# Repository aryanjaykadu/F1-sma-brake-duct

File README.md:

# Passive SMA Brake Duct: feasibility study

Can a brake-cooling duct open and close itself, with no electronics, using a
shape-memory-alloy (Nitinol) spring heated by the brake disc?

The idea: louvers in the duct stay shut on the straights to cut drag, and a
spring heated by the rotor opens them after heavy braking.
I modelled the mechanism in SOLIDWORKS, ran thermal and aero CFD in ANSYS
Fluent, checked the structure in ANSYS MAPDL, and tested the actuator
behaviour over a simulated lap.

**Start here:** [Project Guidebook (PDF)](report/Project_Guidebook.pdf), which covers the problem, how it works, every
phase, tools, results and limits. A web version is in [docs/GUIDEBOOK.md](docs/GUIDEBOOK.md).

Product package: [one-page product sheet](report/SMA_Duct_Module_Product_Sheet.pdf),
[assembly drawing SMA-DM-001](cad/product/SMA-DM-001.pdf),
[design notes](docs/PRODUCT.md).

## What I found

| Question | Answer | Evidence |
|---|---|---|
| Does the linkage give enough stroke? | Yes: 14.0 mm rod travel for 80° of louver rotation | SOLIDWORKS mates, `cad/` |
| Is air near the rotor hot enough to trigger the spring? | No: 300-324 K against the 358 K needed | Fluent, `cfd/Temp_Contour_CaseA*.png` |
| Can rotor radiation trigger it? | Yes, if the wire is dark (emissivity ≥ ~0.45) | 119-129 kW/m² incident, `cfd/SMA_Wire_Temperature_CaseA.png` |
| Does it close again on the straight? | Yes: wire settles at 306-311 K | Fluent Case B |
| Does the specified 1.2 mm NiTi spring work over a lap? | No. It is too slow to heat and its hysteresis is too wide | `cfd/transient/` |
| Redesign | Six 0.5 mm NiTiCu springs (Af 76 °C, Mf 58 °C). They open after the 3 hardest braking zones and are open 2 % of straight-line time | `cfd/transient/`, `fea/pack_NiTiCu/` |
| Stresses OK? | Yes, lowest factor of safety 3.3 | MAPDL, `fea/` |
| Does closing the louvers cut drag by 18.4 %, as the brief assumed? | **No. With a rotating wheel on a moving road, closing them adds 0.5 % drag** | Isolated-wheel Fluent, `cfd/wheel/` |
| Where does the idea pay off? | On an EV grille shutter: closing it cuts drag 14.5 % on a simple CFD car, and about 3-5 % of battery energy on a real one | `ev/`, `docs/EV_COOLING.md` |

The drag result is the main finding, reached in three steps:

1. **Scale.** The duct's own through-flow drag is the momentum of the air it
   swallows: 0.155-0.183 kg/s × 83 m/s ≈ 13-15 N, or 1.1-1.4 % of total drag
   on every mesh. Closing the inlet also changes the outside flow
   (interference), so this is not a hard cap, but 18 % would need
   interference more than ten times larger.
2. **Mesh study, stationary wheel.** On 284k, 408k and 768k cells the
   open-vs-closed difference (-9.6 %, +5.2 %, -1.3 %) stayed within the
   solver noise from the unsteady wheel wake.
3. **Rotating wheel on a moving road, time-averaged over 160 ms of transient
   flow.** Closing the louvers *adds* 0.53 % drag (95 % interval +0.43 to
   +0.63 %). The duct's own drag falls by 0.4 N, but the wheel's rises by
   more.

The full numbers, method and limits are in [docs/RESULTS.md](docs/RESULTS.md),
and the write-up is in [report/ThermoKinetic_BrakeDuct_Whitepaper.pdf](report/ThermoKinetic_BrakeDuct_Whitepaper.pdf).

## Bench rig (designed and virtually tested, not built yet)

The next step is a bench rig that heats the spring pack the way the braking
rotor does and cools it the way the airflow does, so the simulations can be
checked against measurements. It has a halogen lamp standing in for the rotor
and a blower standing in for car speed, with thermocouples, a magnetic angle
sensor and a load cell. It consists of:

- **Rig CAD:** SOLIDWORKS assembly with zero interferences.
- **Electronics:** an Arduino Uno shield in KiCad. ERC and DRC are clean, and
  Gerbers are ready to order.
- **Firmware:** compiled for the Uno, using 57 % of flash and 55 % of RAM.
- **Digital twin:** runs the same firmware code against a physics model of the
  rig. The Phase 4 logger connects to it over a TCP "serial port".

| Virtual test | Twin result |
|---|---|
| Slow ramp hysteresis | Opens 72-75 °C, closes 63-60 °C, 11.5 °C wide (design 12 °C) |
| 0.5 mm vs 1.2 mm wire | Closes in 1.9 s vs 5.7 s |
| Car lap replayed on the rig | Same 3 openings per lap as the car model, 87 % open/closed agreement |
| 1,000 heat/cool cycles | All complete, no firmware faults (no fatigue model) |
| Sensor and cooling failures | Heater latches off in both cases |

The twin also caught design problems before anything was built:

- **Heater switching window:** at 1 s it distorted the hysteresis measurement,
  so it is now 200 ms.
- **Rig capacity:** the first layout was too weak to reproduce the car lap, so
  a blower was added and the lamp moved closer.
- **Phase 1 CAD bug:** the linkage rod was sitting on the wrong side of the duct.

Details are in [docs/RIG.md](docs/RIG.md).

## Product package

The actuator is also detailed as a product:
- **Module CAD:** production-level detail, including real helical NiTiCu
  springs with a black coating, a steel bias spring, anodised brackets and an
  inlet flange with M3 fasteners. 21 components, zero interferences.
- **Animation:** the springs genuinely stretch and contract as the louvers
  open and close.
- **Drawing:** A3 assembly drawing SMA-DM-001 with a parts list.
- **Product sheet:** one-page summary.
- **Rig CAD:** the bench rig now carries the real 3D circuit board exported
  from KiCad.

See [docs/PRODUCT.md](docs/PRODUCT.md).

## Re-target: passive grille shutter for an EV

F1 bans moving aero parts and the brake duct moves too little air to
matter, so I moved the same idea to where it can pay: an EV radiator
shutter. A low-temperature NiTi spring pack (As 35 / Af 40 °C) sits in the
coolant return line and opens six louvers when the coolant warms. It needs
no motor, sensor or wiring.

- **CFD, half car with a porous radiator and moving road:**
  - Closing the shutters cuts drag by 105 N at 100 km/h and 182 N at
    130 km/h, both 14.5 %. Iteration noise is under ±10 N, and the saving
    scales with V².
  - About three quarters of the saving is interference from the plain
    floor exit, not the radiator's own momentum drag.
- **Drive-cycle model, with cooling drag in the road load:**
  - At a production-car level of cooling drag the shutter saves 3.4 % of
    battery energy in the city and 5.4 % at 130 km/h. A motorised
    thermostat shutter saves 4.5 %.
  - On a 38 °C day it opens fully and the coolant peak matches an open
    grille.
- **Module CAD:** frame, six louvers, a scotch-yoke bar (14.8 mm lift for
  80°), the SMA pack in a clear coolant sleeve and a bias spring. Zero
  interferences shut and open.

See [docs/EV_COOLING.md](docs/EV_COOLING.md).

## Limits (read before quoting numbers)

- ANSYS Student licence: meshes are capped at 1M cells, so the CFD is coarse.
- Drag study: the rotating-wheel result is averaged over only 160 ms (about
  four wake cycles) on one mesh, and its 95 % interval covers sampling noise
  only. The drag coefficient (1.19) is still above real-wheel values.
- The lap model is reduced-order, on a synthetic lap trace, calibrated to two
  steady Fluent cases.
- The NiTiCu transformation temperatures are design targets, not a datasheet
  alloy.
- **No hardware was built or tested.** The bench file in `bench/` is a
  simulated dry run of the data logger, and the rig results in
  `bench/virtual/` come from the digital twin, not measurements.
- Moving aero parts are banned under the F1 technical regulations, so this
  is a research and non-FIA concept.

## Tools

SOLIDWORKS 2025, ANSYS Student 2026 R1 (Fluent, MAPDL), KiCad 10,
Arduino (Uno), C++, gmsh and Python.

## Repo layout

| Path | Contents |
|---|---|
| `phase1_*.py`, `swlib.py` | SOLIDWORKS parts and assembly |
| `phase2_*.py` | Fluent CHT domain, meshing, solves, radiation, lap model, wheel aero |
| `phase3_fea.py` | MAPDL linkage and stress model |
| `phase4_bench_validation.py` | DAQ logger (only run in simulation) |
| `phase5_generate_whitepaper.py` | Builds the PDF from the result files |
| `rig_cad.py`, `rig_import_pcb.py` | SOLIDWORKS bench rig parts and assembly, shield PCB import |
| `product_*.py` | Product module CAD, animation, drawing and product sheet |
| `electronics/` | KiCad shield: schematic and PCB generators, Gerbers, BOM |
| `firmware/` | Arduino firmware, lap-profile generator, digital twin and test campaign |
| `ev/` | EV grille-shutter re-target: sizing, half-car CFD, drive-cycle model, shutter CAD |
| `cad/`, `cfd/`, `fea/`, `bench/`, `report/` | Models, plots and result JSON |

Solver case and data files (several GB) are not included. Re-running needs
SOLIDWORKS and ANSYS installed. Run order is in
[docs/RESULTS.md](docs/RESULTS.md#re-running).

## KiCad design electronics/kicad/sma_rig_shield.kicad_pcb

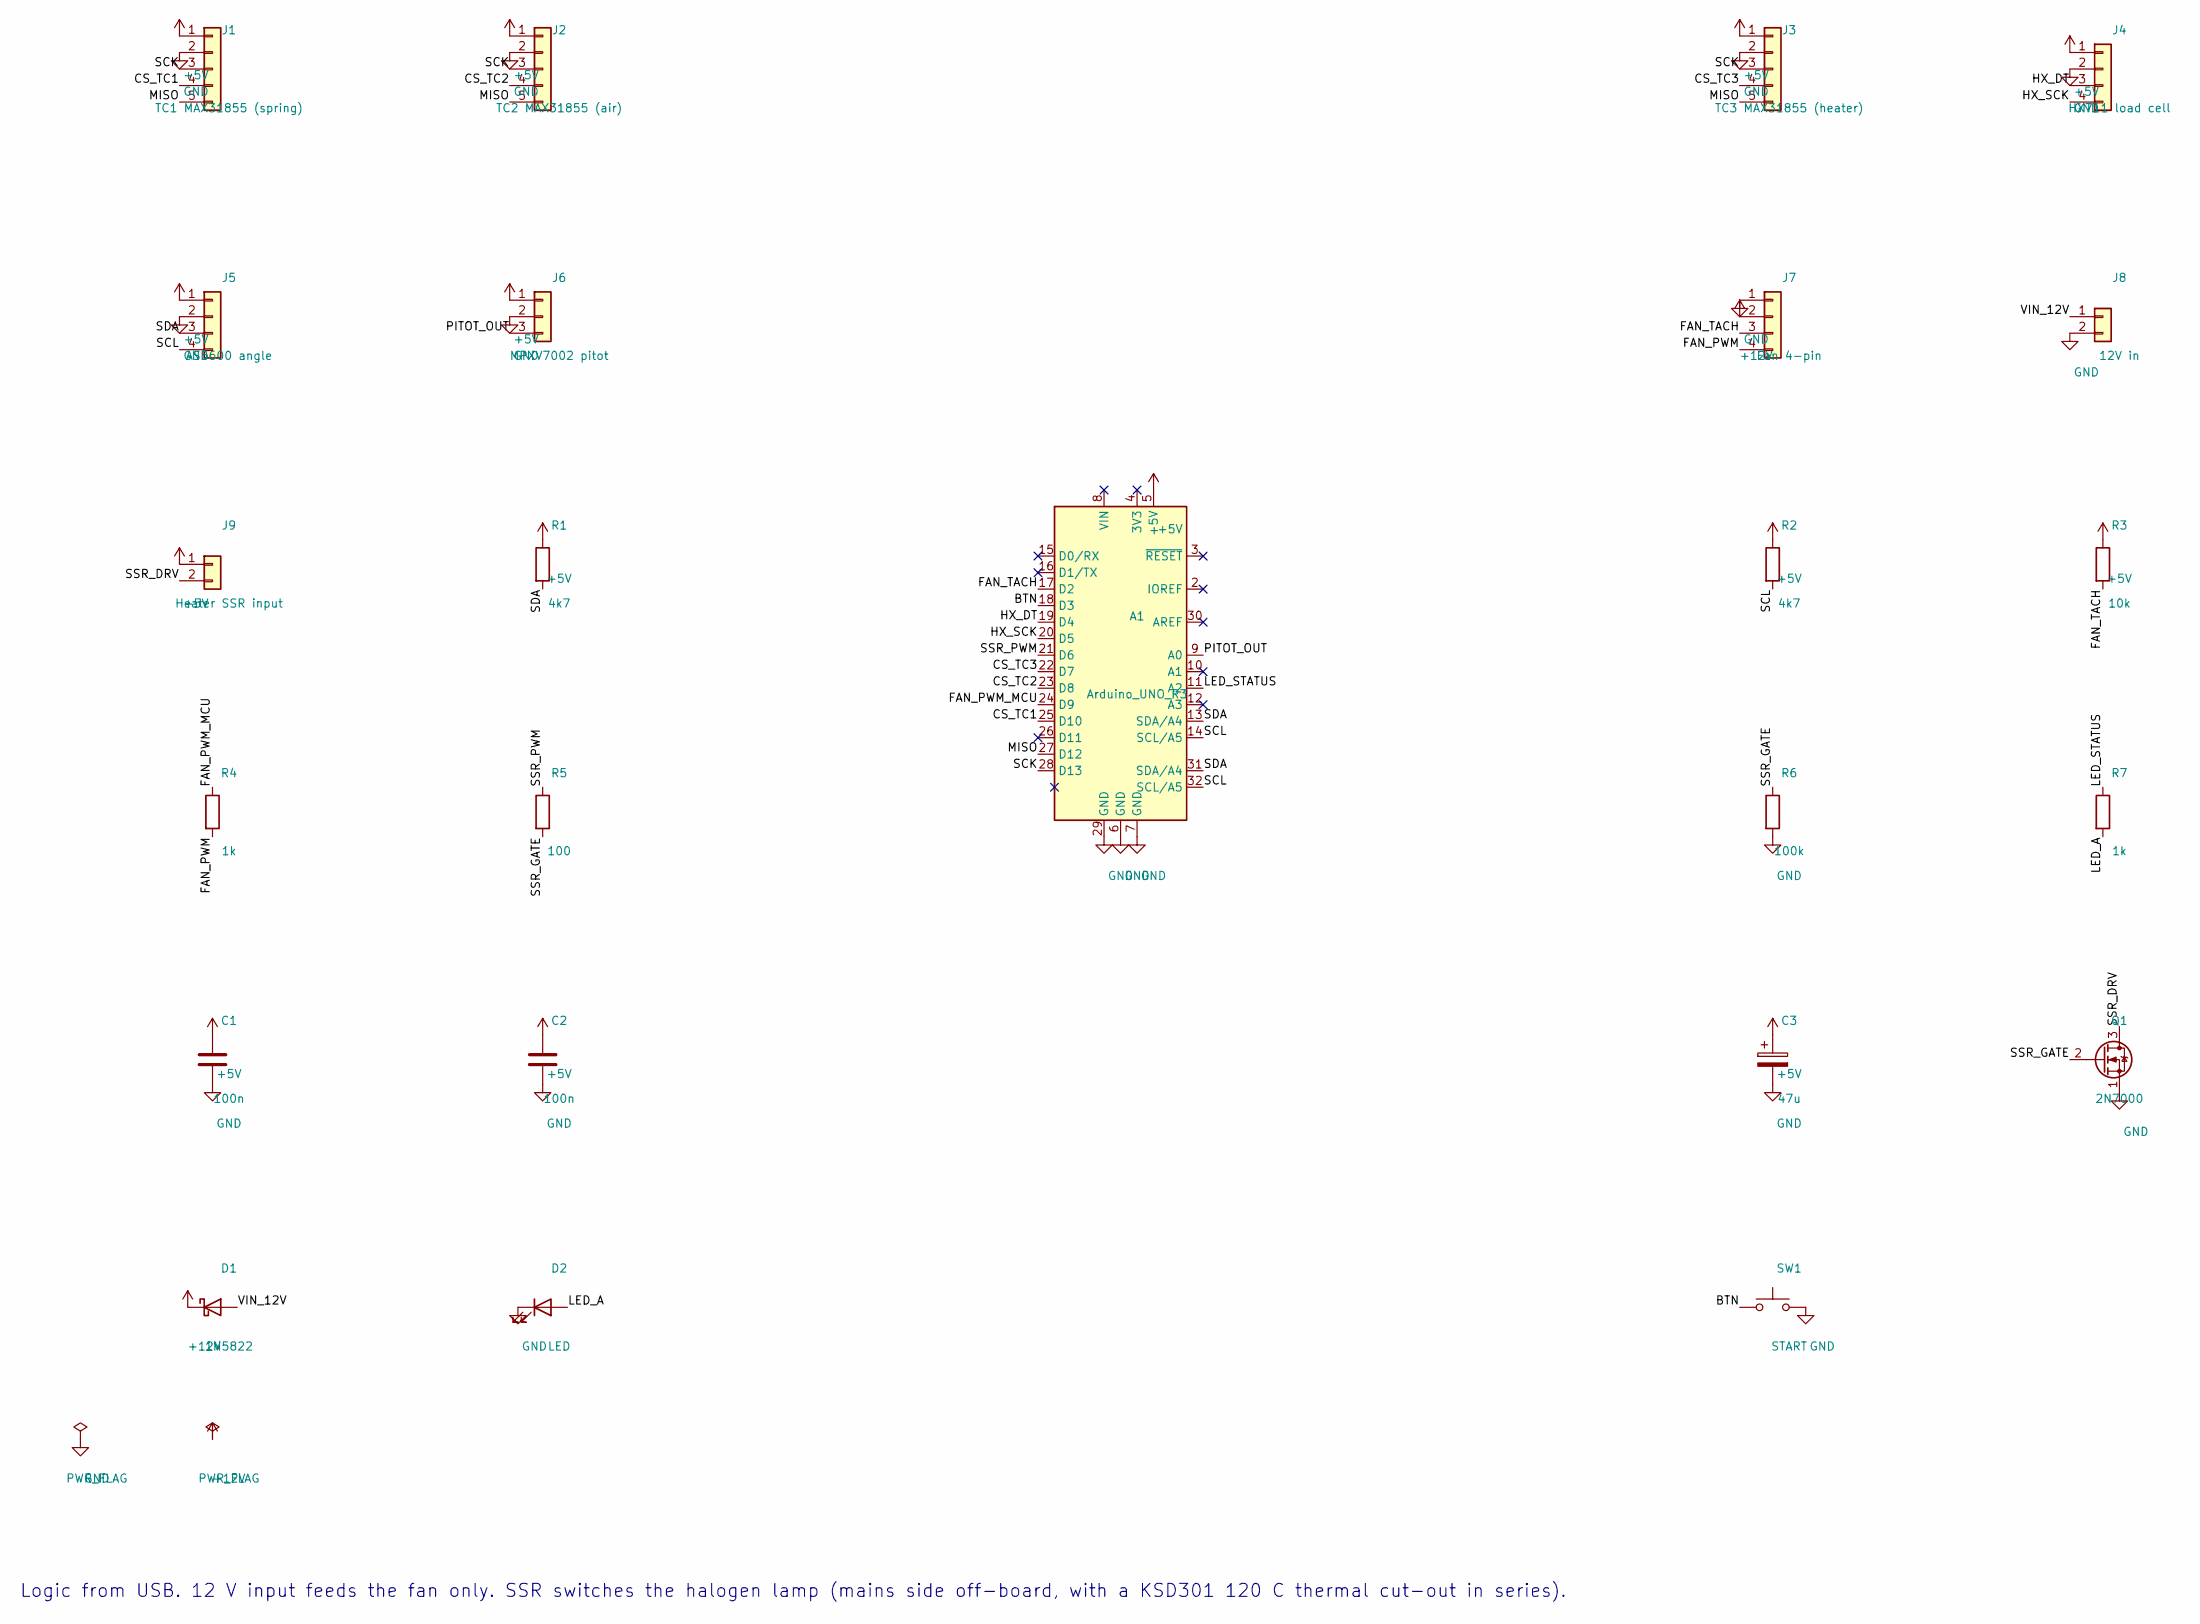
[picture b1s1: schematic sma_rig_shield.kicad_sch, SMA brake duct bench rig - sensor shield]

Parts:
A1: Arduino_UNO_R3; Arduino_UNO_R3_WithMountingHoles
C1, C2: 100n; C_Disc_D5.0mm_W2.5mm_P5.00mm
C3: 47u; CP_Radial_D6.3mm_P2.50mm
D1: 1N5822; D_DO-201AD_P5.08mm_Vertical_AnodeUp
D2: LED; LED_D3.0mm
J1: TC1 MAX31855 (spring); PinSocket_1x05_P2.54mm_Vertical
J2: TC2 MAX31855 (air); PinSocket_1x05_P2.54mm_Vertical
J3: TC3 MAX31855 (heater); PinSocket_1x05_P2.54mm_Vertical
J4: HX711 load cell; PinSocket_1x04_P2.54mm_Vertical
J5: AS5600 angle; PinHeader_1x04_P2.54mm_Vertical
J6: MPXV7002 pitot; PinHeader_1x03_P2.54mm_Vertical
J7: Fan 4-pin; PinHeader_1x04_P2.54mm_Vertical
J8: 12V in; TerminalBlock_Phoenix_MKDS-1,5-2_1x02_P5.00mm_Horizontal
J9: Heater SSR input; TerminalBlock_Phoenix_MKDS-1,5-2_1x02_P5.00mm_Horizontal
Q1: 2N7000; TO-92_Inline
R1, R2: 4k7; R_Axial_DIN0207_L6.3mm_D2.5mm_P7.62mm_Horizontal
R3: 10k; R_Axial_DIN0207_L6.3mm_D2.5mm_P7.62mm_Horizontal
R4, R7: 1k; R_Axial_DIN0207_L6.3mm_D2.5mm_P7.62mm_Horizontal
R5: 100; R_Axial_DIN0207_L6.3mm_D2.5mm_P7.62mm_Horizontal
R6: 100k; R_Axial_DIN0207_L6.3mm_D2.5mm_P7.62mm_Horizontal
SW1: START; SW_PUSH_6mm

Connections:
+5V: A1.5 (+5V), C1.1, C2.1, C3.1, J1.1, J2.1, J3.1, J4.1, J5.1, J6.1, J9.1, R1.1, R2.1, R3.1
+12V: D1.1 (K), J7.2
/BTN: A1.18 (D3), SW1.1
/CS_TC1: A1.25 (D10), J1.4
/CS_TC2: A1.23 (D8), J2.4
/CS_TC3: A1.22 (D7), J3.4
/FAN_PWM: J7.4, R4.2
/FAN_PWM_MCU: A1.24 (D9), R4.1
/FAN_TACH: A1.17 (D2), J7.3, R3.2
/HX_DT: A1.19 (D4), J4.3
/HX_SCK: A1.20 (D5), J4.4
/LED_A: D2.2 (A), R7.2
/LED_STATUS: A1.11 (A2), R7.1
/MISO: A1.27 (D12), J1.5, J2.5, J3.5
/PITOT_OUT: A1.9 (A0), J6.3
/SCK: A1.28 (D13), J1.3, J2.3, J3.3
/SCL: A1.14 (SCL/A5), A1.32 (SCL/A5), J5.4, R2.2
/SDA: A1.13 (SDA/A4), A1.31 (SDA/A4), J5.3, R1.2
/SSR_DRV: J9.2, Q1.3 (D)
/SSR_GATE: Q1.2 (G), R5.2, R6.1
/SSR_PWM: A1.21 (D6), R5.1
/VIN_12V: D1.2 (A), J8.1
GND: A1.6 (GND), A1.7 (GND), A1.29 (GND), C1.2, C2.2, C3.2, D2.1 (K), J1.2, J2.2, J3.2, J4.2, J5.2, J6.2, J7.1, J8.2, Q1.1 (S), R6.2, SW1.2

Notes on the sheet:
Logic from USB. 12 V input feeds the fan only. SSR switches the halogen lamp (mains side off-board, with a KSD301 120 C thermal cut-out in series).

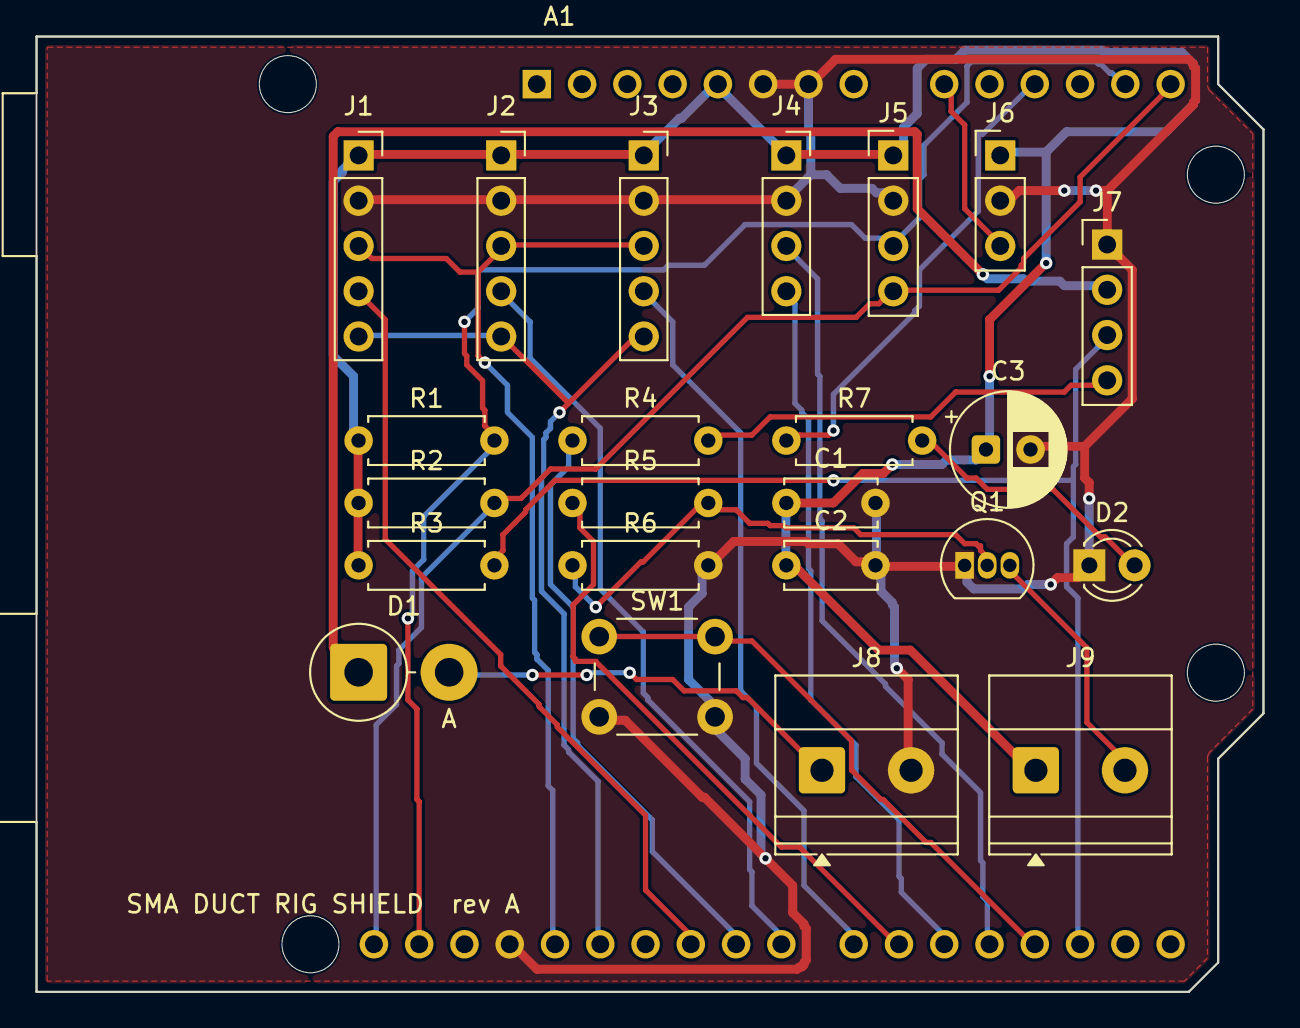
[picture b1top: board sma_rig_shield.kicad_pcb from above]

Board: 2 copper layers, 68.8 x 53.6 mm, 24 parts (0 on the bottom side), 23 nets.

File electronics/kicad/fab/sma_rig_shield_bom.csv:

"Refs","Value","Footprint","Qty","DNP"
"A1","Arduino_UNO_R3","Module:Arduino_UNO_R3_WithMountingHoles","1",""
"C1","100n","Capacitor_THT:C_Disc_D5.0mm_W2.5mm_P5.00mm","1",""
"C2","100n","Capacitor_THT:C_Disc_D5.0mm_W2.5mm_P5.00mm","1",""
"C3","47u","Capacitor_THT:CP_Radial_D6.3mm_P2.50mm","1",""
"D1","1N5822","Diode_THT:D_DO-201AD_P5.08mm_Vertical_AnodeUp","1",""
"D2","LED","LED_THT:LED_D3.0mm","1",""
"J1","TC1 MAX31855 (spring)","Connector_PinSocket_2.54mm:PinSocket_1x05_P2.54mm_Vertical","1",""
"J2","TC2 MAX31855 (air)","Connector_PinSocket_2.54mm:PinSocket_1x05_P2.54mm_Vertical","1",""
"J3","TC3 MAX31855 (heater)","Connector_PinSocket_2.54mm:PinSocket_1x05_P2.54mm_Vertical","1",""
"J4","HX711 load cell","Connector_PinSocket_2.54mm:PinSocket_1x04_P2.54mm_Vertical","1",""
"J5","AS5600 angle","Connector_PinHeader_2.54mm:PinHeader_1x04_P2.54mm_Vertical","1",""
"J6","MPXV7002 pitot","Connector_PinHeader_2.54mm:PinHeader_1x03_P2.54mm_Vertical","1",""
"J7","Fan 4-pin","Connector_PinHeader_2.54mm:PinHeader_1x04_P2.54mm_Vertical","1",""
"J8","12V in","TerminalBlock_Phoenix:TerminalBlock_Phoenix_MKDS-1,5-2_1x02_P5.00mm_Horizontal","1",""
"J9","Heater SSR input","TerminalBlock_Phoenix:TerminalBlock_Phoenix_MKDS-1,5-2_1x02_P5.00mm_Horizontal","1",""
"Q1","2N7000","Package_TO_SOT_THT:TO-92_Inline","1",""
"R1","4k7","Resistor_THT:R_Axial_DIN0207_L6.3mm_D2.5mm_P7.62mm_Horizontal","1",""
"R2","4k7","Resistor_THT:R_Axial_DIN0207_L6.3mm_D2.5mm_P7.62mm_Horizontal","1",""
"R3","10k","Resistor_THT:R_Axial_DIN0207_L6.3mm_D2.5mm_P7.62mm_Horizontal","1",""
"R4","1k","Resistor_THT:R_Axial_DIN0207_L6.3mm_D2.5mm_P7.62mm_Horizontal","1",""
"R5","100","Resistor_THT:R_Axial_DIN0207_L6.3mm_D2.5mm_P7.62mm_Horizontal","1",""
"R6","100k","Resistor_THT:R_Axial_DIN0207_L6.3mm_D2.5mm_P7.62mm_Horizontal","1",""
"R7","1k","Resistor_THT:R_Axial_DIN0207_L6.3mm_D2.5mm_P7.62mm_Horizontal","1",""
"SW1","START","Button_Switch_THT:SW_PUSH_6mm","1",""

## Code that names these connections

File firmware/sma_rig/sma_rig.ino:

// sma_rig.ino - Arduino UNO R3 firmware for the SMA brake-duct bench rig (sensor shield rev A).
// Hardware layer only: sensors in, SSR / fan / LED out. All logic lives in rig_core.{h,cpp}.
//
// Pins (shield schematic):
//   D13 SCK, D12 MISO, D10/D8/D7  MAX31855 CS for TC1 spring / TC2 air / TC3 reflector
//   A4 SDA, A5 SCL                AS5600 louver angle
//   D4 DT, D5 SCK                 HX711 load cell
//   D9 fan PWM 25 kHz (Timer1), D2 fan tach (INT0), D6 heater SSR, D3 button, A2 LED, A0 pitot
#include <SPI.h>
#include <Wire.h>
#include <Adafruit_MAX31855.h>
#include <AS5600.h>
#include <HX711.h>

#include "rig_core.h"

const uint8_t PIN_CS_TC1 = 10, PIN_CS_TC2 = 8, PIN_CS_TC3 = 7;
const uint8_t PIN_HX_DT = 4, PIN_HX_SCK = 5;
const uint8_t PIN_FAN_PWM = 9, PIN_TACH = 2, PIN_SSR = 6, PIN_BTN = 3;
const uint8_t PIN_LED = A2, PIN_PITOT = A0;

Adafruit_MAX31855 tc1(PIN_CS_TC1), tc2(PIN_CS_TC2), tc3(PIN_CS_TC3);
AS5600 encoder;
HX711 loadcell;
rig::Core core;
rig::Inputs in;
rig::Outputs out;

volatile uint32_t tachPulses = 0;
void onTach() { tachPulses++; }

char line[48];
uint8_t lineLen = 0;
char tx[240];

void fanBegin() {
  pinMode(PIN_FAN_PWM, OUTPUT);
  TCCR1A = _BV(COM1A1) | _BV(WGM11);               // fast PWM, TOP = ICR1, non-inverting on OC1A (D9)
  TCCR1B = _BV(WGM13) | _BV(WGM12) | _BV(CS10);    // no prescaler
  ICR1 = 639;                                       // 16 MHz / 640 = 25 kHz (Intel 4-pin fan spec)
  OCR1A = 0;
}

void fanSet(uint8_t pct) { OCR1A = (uint16_t)((uint32_t)pct * 639u / 100u); }

void readThermocouples() {
  static uint32_t last = 0;
  if (millis() - last < 100) return;                // MAX31855 converts at ~10 Hz
  last = millis();
  double t;
  t = tc1.readCelsius(); in.t_spring_ok = !isnan(t); if (in.t_spring_ok) in.t_spring_c = (float)t;
  t = tc2.readCelsius(); in.t_air_ok = !isnan(t);    if (in.t_air_ok) in.t_air_c = (float)t;
  t = tc3.readCelsius(); in.t_heater_ok = !isnan(t); if (in.t_heater_ok) in.t_heater_c = (float)t;
}

void readButton() {
  static uint8_t stable = 0, last = 0;
  static uint32_t changed = 0;
  uint8_t raw = digitalRead(PIN_BTN) == LOW;
  if (raw != last) { last = raw; changed = millis(); }
  if (millis() - changed > 30) stable = raw;
  in.button = stable;
}

void pollSerial() {
  while (Serial.available()) {
    char c = (char)Serial.read();
    if (c == '\n' || c == '\r') {
      if (lineLen) { line[lineLen] = 0; core.command(line); lineLen = 0; }
    } else if (lineLen < sizeof(line) - 1) {
      line[lineLen++] = c;
    }
  }
}

void setup() {
  Serial.begin(115200);
  pinMode(PIN_SSR, OUTPUT);
  digitalWrite(PIN_SSR, LOW);
  pinMode(PIN_LED, OUTPUT);
  pinMode(PIN_BTN, INPUT_PULLUP);
  pinMode(PIN_TACH, INPUT);                          // 10k pull-up on the shield
  attachInterrupt(digitalPinToInterrupt(PIN_TACH), onTach, FALLING);
  fanBegin();
  tc1.begin(); tc2.begin(); tc3.begin();
  Wire.begin();
  encoder.begin();
  loadcell.begin(PIN_HX_DT, PIN_HX_SCK);
  delay(250);                                        // MAX31855 first conversion
  core.begin(millis());
}

void loop() {
  pollSerial();
  readThermocouples();
  readButton();
  in.load_ready = loadcell.is_ready();
  if (in.load_ready) in.load_raw = (int32_t)loadcell.read();
  in.angle_ok = encoder.isConnected();
  if (in.angle_ok) in.angle_raw = encoder.readAngle();
  noInterrupts();
  in.tach_count = tachPulses;
  interrupts();
  in.pitot_adc = analogRead(PIN_PITOT);
  in.now_ms = millis();

  core.update(in, out);
  digitalWrite(PIN_SSR, out.heater_on ? HIGH : LOW);
  fanSet(out.fan_pct);
  digitalWrite(PIN_LED, out.led_on ? HIGH : LOW);

  if (core.pending_message(tx, sizeof(tx))) Serial.println(tx);
  if (core.telemetry(tx, sizeof(tx))) Serial.println(tx);
}
